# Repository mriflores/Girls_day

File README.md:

# 433MHz RF Communication Project with ID Filtering & Servo Control

This project implements a wireless communication system between two Arduino boards using 433MHz Radio Frequency modules. It features a custom ID filtering system to ensure messages are processed only by the intended receiver, and allows for remote control of a servo motor.

---

## Hardware Configuration

### Components Required
* **Microcontrollers:** 2x Arduino Uno.
* **RF Kit:** 2x 433MHz Transmitter (FS1000A), 1x 433MHz Receiver (XY-MX-5V).
* **Actuator:** 1x Servo Motor (e.g., SG90, MG996R).
* **Antennas:** 4x 17.3 cm copper wires (Required for range beyond 10cm).

### RF Wiring Diagram

| RF Module | Arduino Pin | Description |
| :--- | :--- | :--- |
| **Transmitter DATA** | D12 | Data Output |
| **Transmitter VCC** | 5V | Power (Up to 12V for range) |
| **Transmitter GND** | GND | Ground |
| **Receiver DATA** | D11 | Data Input |
| **Receiver VCC** | 5V | Power (Must be stable 5V) |
| **Receiver GND** | GND | Ground |

### Servo Wiring Diagram

| Servo | Arduino Pin | Description |
| :--- | :--- | :--- |
| **Signal (Orange/Yellow)**| D2 | PWM Control Signal |
| **VCC (Red)** | 5V | Power (External power recommended for larger servos) |
| **GND (Brown/Black)** | GND | Ground |

---

## Technical Implementation & Dependencies

The system relies on specific libraries to manage the communication and motor control without hardware timer conflicts:

* **RadioHead (RH_ASK):** Handles the physical layer bit-streaming, preamble, and CRC error checking for the RF modules. It inherently relies on Arduino's Timer 1.
* **ServoTimer2:** Manages the PWM signals for the servo motor. Using this library instead of the standard Arduino `Servo.h` is necessary to prevent Timer 1 conflicts, ensuring both RF communication and servo movements work seamlessly together.

---

## Features

* **Targeted Messaging:** Uses custom ID prefixes to ensure that only the designated receiver acts on a broadcasted message, ignoring irrelevant data.
* **Remote Actuation:** Wirelessly controls a servo motor, interpreting text strings to execute specific physical movements.
* **Dynamic Pulse Mapping:** Automatically maps standard angle values (0-180 degrees) to microsecond pulse widths for accurate servo positioning.

---

## Command Protocol

The transmitter must format strings with a specific structure for the receiver to validate and act upon them. The structure is: 

`[RECEIVER_ID] [COMMAND]`

### Example Usage:
In this project, the Receiver's ID is set to `100`. Through the Serial Monitor, you can send the following commands:

* **`100 OPEN`**: The receiver parses the ID, confirms a match, and moves the servo to the 90-degree position.
* **`100 CLOSE`**: The receiver parses the ID, confirms a match, and returns the servo to the 0-degree position.

Any message received with an incorrect ID (e.g., `300 OPEN` or just `OPEN`) will be completely ignored by the receiving node.

---

## Important Notes
* **Power Supply:** If the Arduino resets or the RF receiver stops working when the servo moves, it is highly recommended to power the servo with a separate 5V power supply. Remember to connect the ground (GND) of the external power supply to the Arduino's GND.

---

The uploaded image illustrates the specific wiring connections for two separate microcontroller nodes capable of two-way RF communication.

**Node 1** (Top Section)
    This node acts as the primary controller equipped with actuation capabilities.

* Microcontroller: Arduino Uno (U1).

* RF Transmitter (U2 - FS1000A): The Data pin is wired to digital pin D12 (blue wire).

* RF Receiver (U3 - XY-MK-5V): The Data pin is wired to digital pin D11 (green wire).

* Servo Motor (U4): The PWM signal pin is wired to digital pin D2 (orange wire).

Power: All three peripherals (U2, U3, U4) share common 5V (red wires) and Ground (black wires) connections drawn directly from the Arduino Uno.

**Node 2** (Bottom Section)
    This node acts as the secondary transceiver.

* Microcontroller: A compact Arduino board, such as a Nano or Micro (U5).

* RF Transmitter (U6 - FS1000A): The Data pin is wired to digital pin D12 (blue wire).

* RF Receiver (U7 - XY-MK-5V): The Data pin is wired to digital pin D11 (green wire).

Power: Both RF modules draw 5V (red wires) and Ground (black wires) from the compact Arduino board.

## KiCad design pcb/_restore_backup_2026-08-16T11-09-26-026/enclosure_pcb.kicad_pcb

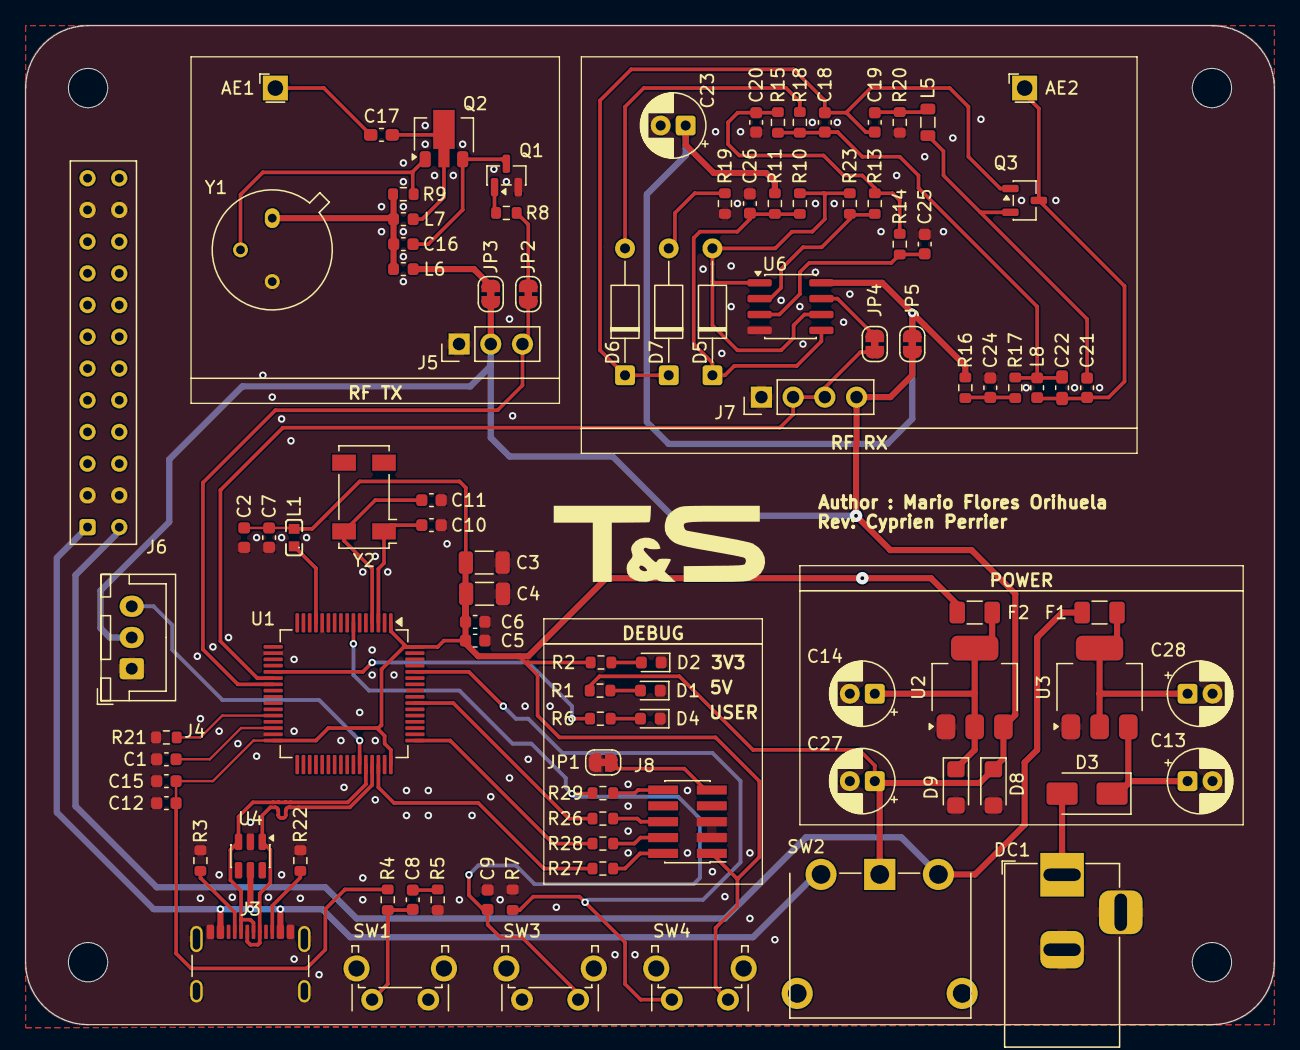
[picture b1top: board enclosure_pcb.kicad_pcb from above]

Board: 2 copper layers, 100.0 x 80.0 mm, 102 parts (0 on the bottom side), 60 nets.

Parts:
AE1, AE2: Antenna; AntennaHole
C1, C26: 4.7uF; C_0603_1608Metric
C2, C9: 100nF; C_0603
C3, C4: 100nF; C_1206_3216Metric
C5, C6, C8: 100nF; C_0603_1608Metric
C7, C12, C15, C25: 1uF; C_0603_1608Metric
C10, C11: 6.8pF; C_0603_1608Metric
C13: 1uF; CP_Radial_D5.0mm_P2.00mm
C14: 100uF; CP_Radial_D5.0mm_P2.00mm
C16: 7pF; C_0603_1608Metric
C17: 7pF; C_0603_1608Metric_Pad1.08x0.95mm_HandSolder
C18: 33pF; C_0603_1608Metric
C19, C20: 1nF; C_0603_1608Metric
C21: 2pF; C_0603_1608Metric
C22: 2pF; C_0603_1608Metric_Pad1.08x0.95mm_HandSolder
C23, C27: 10uF; CP_Radial_D5.0mm_P2.00mm
C24: 47uF; C_0603_1608Metric
C28: 4.7uF; CP_Radial_D5.0mm_P2.00mm
D1, D2: VLMS1300-GS08; LED_0603_1608Metric
D3: D; D_SMA
D4: Blue; LED_0603_1608Metric
D5, D6, D7: 1N4148_C402212; D_DO-35_SOD27_P10.16mm_Horizontal
D8: PLZ5V1B; D_SMF
D9: PLZ3V3B; D_SMF
DC1: DC-005-A200; BarrelJack_Horizontal
F1, F2: Polyfuse; Fuse_1206_3216Metric
H2, H3, H4, H5: MountingHole; MountingHole_2.1mm
J3: USB_C_Receptacle_USB2.0_14P; USB_C_Receptacle_GCT_USB4105-xx-A_16P_TopMnt_Horizontal
J4: Conn_01x03_Pin; JST_XH_B3B-XH-A_1x03_P2.50mm_Vertical
J5: Conn_01x03_Pin; PinHeader_1x03_P2.54mm_Vertical
J6: Conn_02x12_Odd_Even; Samtec_HLE-112-02-xx-DV-TE_2x12_P2.54mm_Horizontal
J7: Conn_01x04_Pin; PinHeader_1x04_P2.54mm_Vertical
J8: Conn_ARM_JTAG_SWD_10; PinHeader_2x05_P1.27mm_Vertical_SMD
JP1, JP2, JP3, JP4, JP5: SolderJumper_2_Bridged; SolderJumper-2_P1.3mm_Bridged_RoundedPad1.0x1.5mm
L1: FCM1608KF-601T05; L0603
L5: 2uH; L_0805_2012Metric
L6: 180nH; L_0603_1608Metric
L7: 36nH; L_0603_1608Metric
L8: 15nH; L_0603_1608Metric
Q1: S8050; SOT-23
Q2: 2SC3357-T1-A; SOT-89-3
Q3: MMBT918; SOT-23-3
R1: 180Ω; R_0603_1608Metric
R2, R5: 100Ω; R_0603_1608Metric
R3, R22: 5k1R; R_0603_1608Metric
R4: 4.7kΩ; R_0603_1608Metric
R6: 47Ω; R_0603_1608Metric
R7: 10kΩ; R_0603
R8, R9: 27kΩ; R_0603_1608Metric
R10: 47kΩ; R_0603_1608Metric
R11: 3MΩ; R_0603_1608Metric
R13, R14: 100kΩ; R_0603_1608Metric
R15: 5.6kΩ; R_0603_1608Metric
R16: 10Ω; R_0603_1608Metric
R17: 12kΩ; R_0603_1608Metric
R18: 20kΩ; R_0603_1608Metric
R19: 18kΩ; R_0603_1608Metric
R20: 680kΩ; R_0603_1608Metric
R21: 10kΩ; R_0603_1608Metric
R23: 6.8MΩ; R_0603_1608Metric
R26, R27, R28, R29: 22Ω; R_0603_1608Metric
SW1, SW3, SW4: SW_Push_WE; SW_Tactile_SPST_Angled_WE
SW2: SW_Lever_RSPRO_5MS1
U1: STM32F446RETx; LQFP-64_10x10mm_P0.5mm
U2: LD1117S33TR_SOT223; SOT-223-3_TabPin2
U3: LD1117S50TR_SOT223; SOT-223-3_TabPin2
U4: USBLC6-4SC6; SOT-23-6
U6: LM358_C5252902; SOIC-8_3.9x4.9mm_P1.27mm
Y1: Crystal_GND3; TO-39-3
Y2: Crystal_4-pin; Crystal_SMD_Abracon_ABS25-4Pin_8.0x3.8mm

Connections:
+3.3VA: L1.1, U1.13 (VDDA)
+3V3: C2.1, C3.1, C4.1, C5.1, C6.1, C7.1, C12.1, C15.1, F2.1, J6.23, J8.1 (VTref), L1.2, R2.1, R4.1, SW4.3, U1.1 (VBAT), U1.19 (VDD), U1.32 (VDD), U1.48 (VDD), U1.64 (VDD)
+5V: C27.1, D8.1 (K), J4.2, J5.2, J6.24, J7.4, JP3.1 (A), JP5.1 (A), R1.1, SW2.2 (B), U2.3 (VI)
+E5V: F1.1, J6.2, SW2.3 (C)
+U5V: J3.A4 (VBUS), J3.A9 (VBUS), J3.B4 (VBUS), J3.B9 (VBUS), J6.1, SW2.1 (A), U4.5 (VBUS)
/SCH_FS1000/5V_FS: JP3.2 (B), L6.1
/SCH_FS1000/5V_XY: C23.1, JP5.2 (B), R11.1, R16.2, U6.8 (VCC)
/SCH_FS1000/DATA IN: J7.2, J7.3, JP4.1 (A), U1.22 (PA6)
/SCH_FS1000/DATA OUT: J5.3, JP2.1 (A), U1.23 (PA7)
/SCH_FS1000/DATA_IN_XY: JP4.2 (B), U6.7 (OUT2)
/SCH_FS1000/DATA_OUT_FS: JP2.2 (B), R8.1
/SCH_MCU/LED: R6.1, U1.21 (PA5)
/SCH_MCU/NRST: C9.2, R29.2, SW3.3, U1.7 (NRST)
/SCH_MCU/OSC32_IN: C10.1, U1.3 (PC14), Y2.1
/SCH_MCU/OSC32_OUT: C11.1, U1.4 (PC15), Y2.4
/SCH_MCU/PUSH_BTN: C8.1, R4.2, SW1.2, U1.2 (PC13)
/SCH_MCU/PWM: J4.3, U1.43 (PA10)
/SCH_MCU/SWCLK: R28.2, U1.49 (PA14)
/SCH_MCU/SWDIO: R27.2, U1.46 (PA13)
/SCH_MCU/SWO: R26.2, U1.55 (PB3)
/SCH_MCU/U_D_N: J3.A7 (D-), J3.B7 (D-), U1.44 (PA11), U4.3 (I/O2)
/SCH_MCU/U_D_P: J3.A6 (D+), J3.B6 (D+), U1.45 (PA12), U4.1 (I/O1)
GND: C1.2, C2.2, C3.2, C4.2, C5.2, C6.2, C7.2, C9.1, C10.2, C11.2, C12.2, C13.2, C14.2, C15.2, C20.2, C23.2, C24.2, C25.2, C26.2, C27.2, C28.2, D1.1 (K), D2.1 (K), D4.1, D8.2 (A), D9.2 (A), DC1.2, DC1.3, J3.A1 (GND), J3.A12 (GND), J3.B1 (GND), J3.B12 (GND), J3.SH (SHIELD), J4.1, J5.1, J6.3, J6.4, J6.21, J6.22, J7.1, J8.3 (GND), J8.5 (GND), JP1.1 (A), Q1.2 (E), R3.1, R5.1, R7.2, R19.2, R20.2, R21.2, R22.2, SW1.1, SW1.3, SW1.4, SW3.1, SW3.2, SW3.4, SW4.1, SW4.4, U1.12 (VSSA), U1.18 (VSS), U1.31 (VSS), U1.47 (VSS), U1.63 (VSS), U2.1 (GND), U3.1 (GND), U4.2 (GND), U6.4 (VEE), Y1.3
unnamed: AE1.1 (A_1), C17.1
unnamed: AE2.1 (A_1), C21.2, C22.1, L8.1, Q3.3 (C)
unnamed: C8.2, R5.2
unnamed: C16.2, L6.2, L7.1, R9.1, Y1.1
unnamed: C18.1, C22.2, L8.2, R15.1, R17.2, R18.1
unnamed: C19.2, L5.1, R20.1
unnamed: C20.1, R13.1, R14.1, R15.2
unnamed: C24.1, R16.1, R17.1
unnamed: D1.2 (A), R1.2
unnamed: D2.2 (A), R2.2
unnamed: D3.2 (A), DC1.1
unnamed: D4.2, R6.2
unnamed: D5.2 (A), R10.1, R23.2, U6.1 (OUT1), U6.6 (IN2-)
unnamed: C26.1, D5.1 (C), R10.2, R11.2, U6.5 (IN2+)
unnamed: D6.2 (A), R18.2
unnamed: C18.2, C19.1, D6.1 (C), D7.1 (C), Q3.1 (B)
unnamed: D7.2 (A), R19.1
unnamed: C14.1, D9.1 (K), F2.2, U2.2 (VO)
unnamed: J3.A5 (CC1), R3.2
unnamed: J3.B5 (CC2), R22.1
unnamed: J8.9 (GNDDetect), JP1.2 (B)
unnamed: J8.4 (SWCLK/TCK), R28.1
unnamed: J8.2 (SWDIO/TMS), R27.1
unnamed: J8.6 (SWO/TDO), R26.1
unnamed: J8.10 (~RESET), R29.1
unnamed: Q1.1 (B), R8.2
unnamed: C16.1, Q1.3 (C), Q2.3 (E)
unnamed: Q2.1 (B), R9.2, Y1.2
unnamed: C17.2, L7.2, Q2.2 (C)
unnamed: C21.1, L5.2, Q3.2 (E)
unnamed: R7.1, SW4.2, U1.60 (BOOT0)
unnamed: R21.1, U1.28 (PB2)
unnamed: C1.1, U1.30 (VCAP_1)
unnamed: C28.1, F1.2, U3.2 (VO)
unnamed: C25.1, R14.2, U6.3 (IN1+)
unnamed: R13.2, R23.1, U6.2 (IN1-)
VIN: C13.1, D3.1 (K), U3.3 (VI)

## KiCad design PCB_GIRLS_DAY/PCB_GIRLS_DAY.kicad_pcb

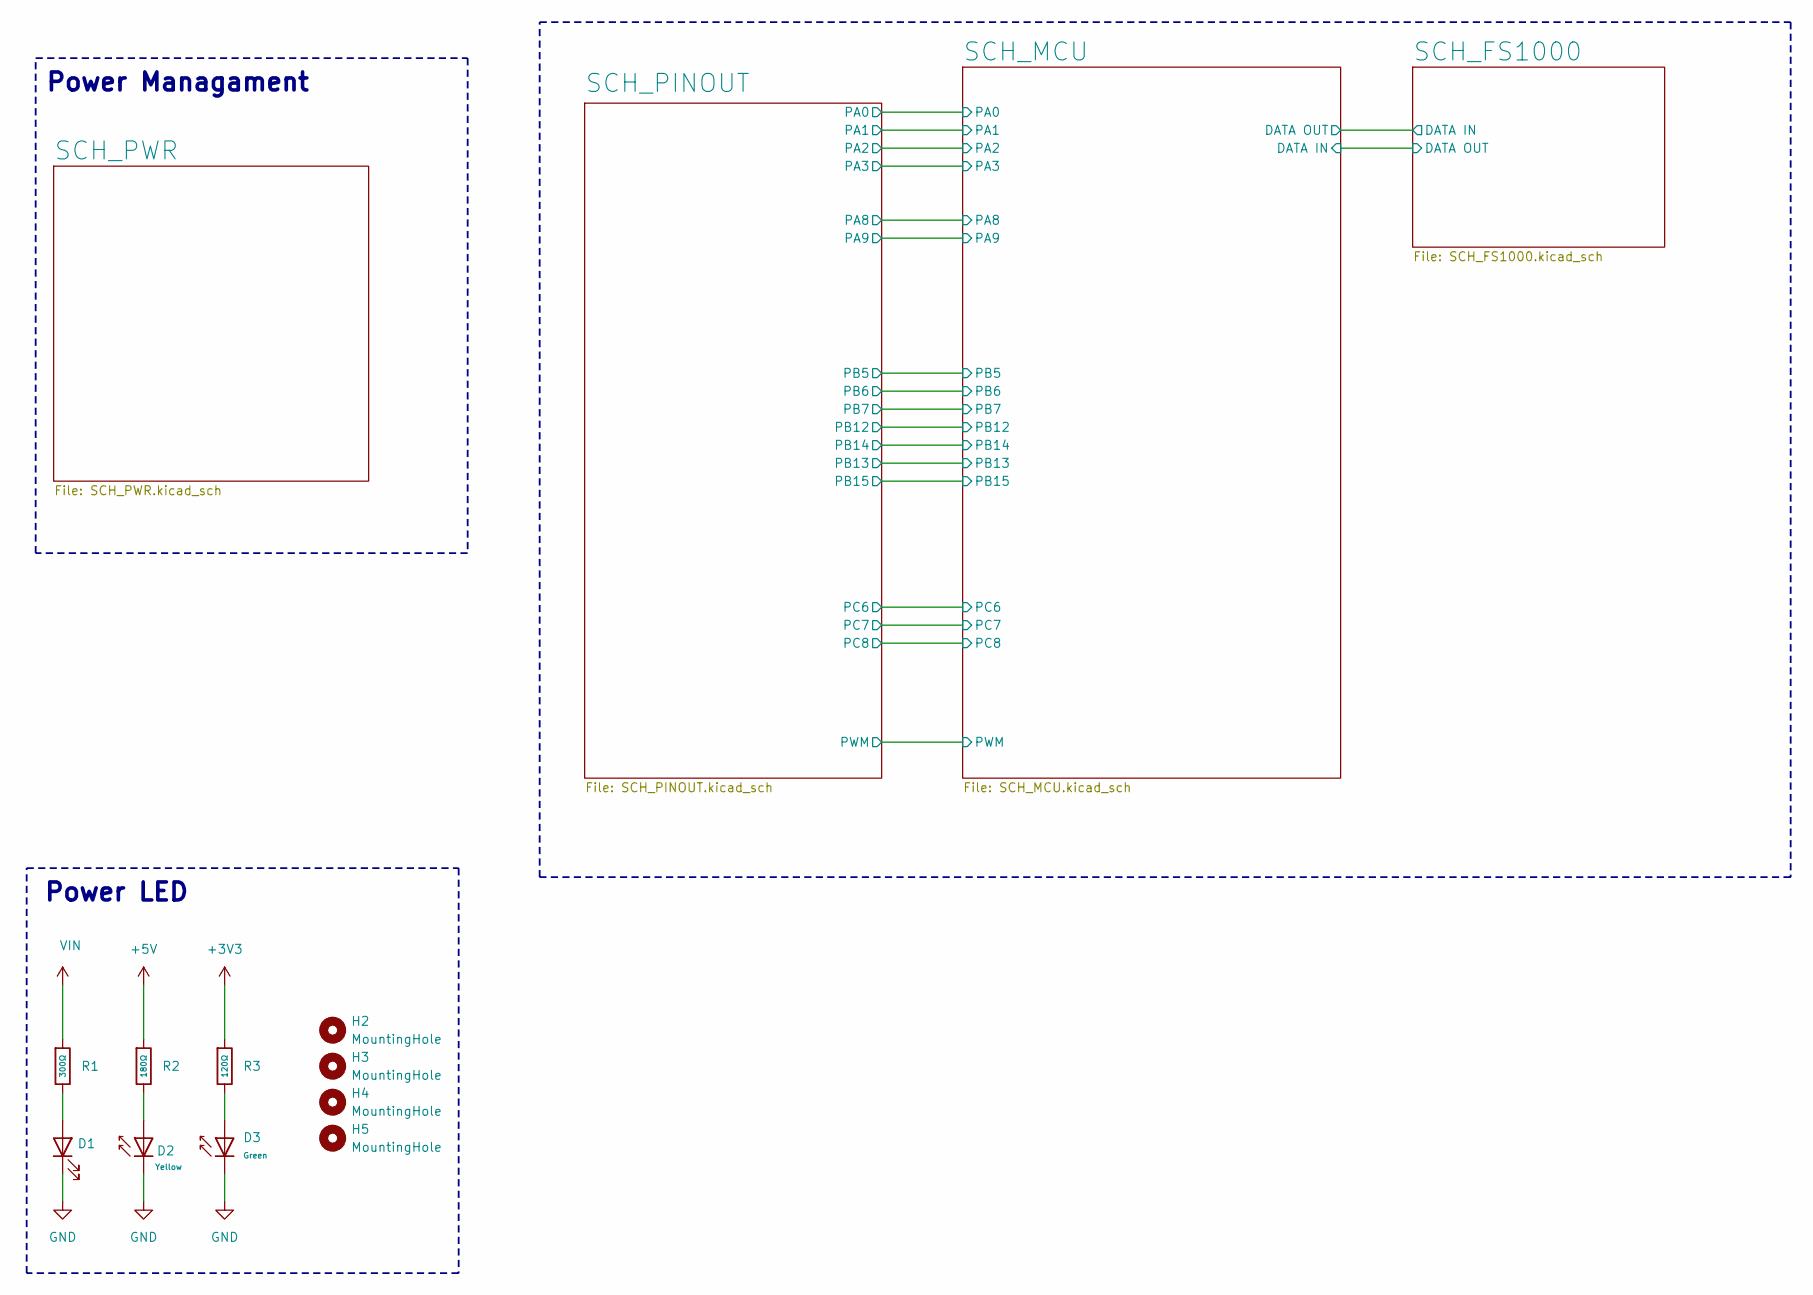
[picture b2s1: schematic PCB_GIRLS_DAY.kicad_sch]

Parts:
D1: IR26-21C_L110_TR8; LED_1206_3216Metric
D2: Yellow; D_0805; Part KT-0805Y; LCSC C2296
D3: Green; D_0805; Part KT-0805G; LCSC C2297
H2, H3, H4, H5: MountingHole; MountingHole_2.1mm
R1: 300Ω; R_1206; Overload Voltage (Max) 200V; Tolerance ±1%; Part 1206W4F3000T5E; LCSC C17887
R2: 180Ω; R_1206; Overload Voltage (Max) 200V; Tolerance ±1%; Part 1206W4F1800T5E; LCSC C17924
R3: 120Ω; R_0805; Overload Voltage (Max) 150V; Tolerance ±1%; Part 0805W8F1200T5E; LCSC C17437

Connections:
+3V3: R3.1; also elsewhere on the board
+5V: R2.1; also elsewhere on the board
GND: D1.1 (K), D2.1, D3.1; also elsewhere on the board
unnamed: D1.2 (A), R1.2
unnamed: D2.2, R2.2
unnamed: D3.2, R3.2
VIN: R1.1; also elsewhere on the board

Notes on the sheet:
Power Managament
Power LED

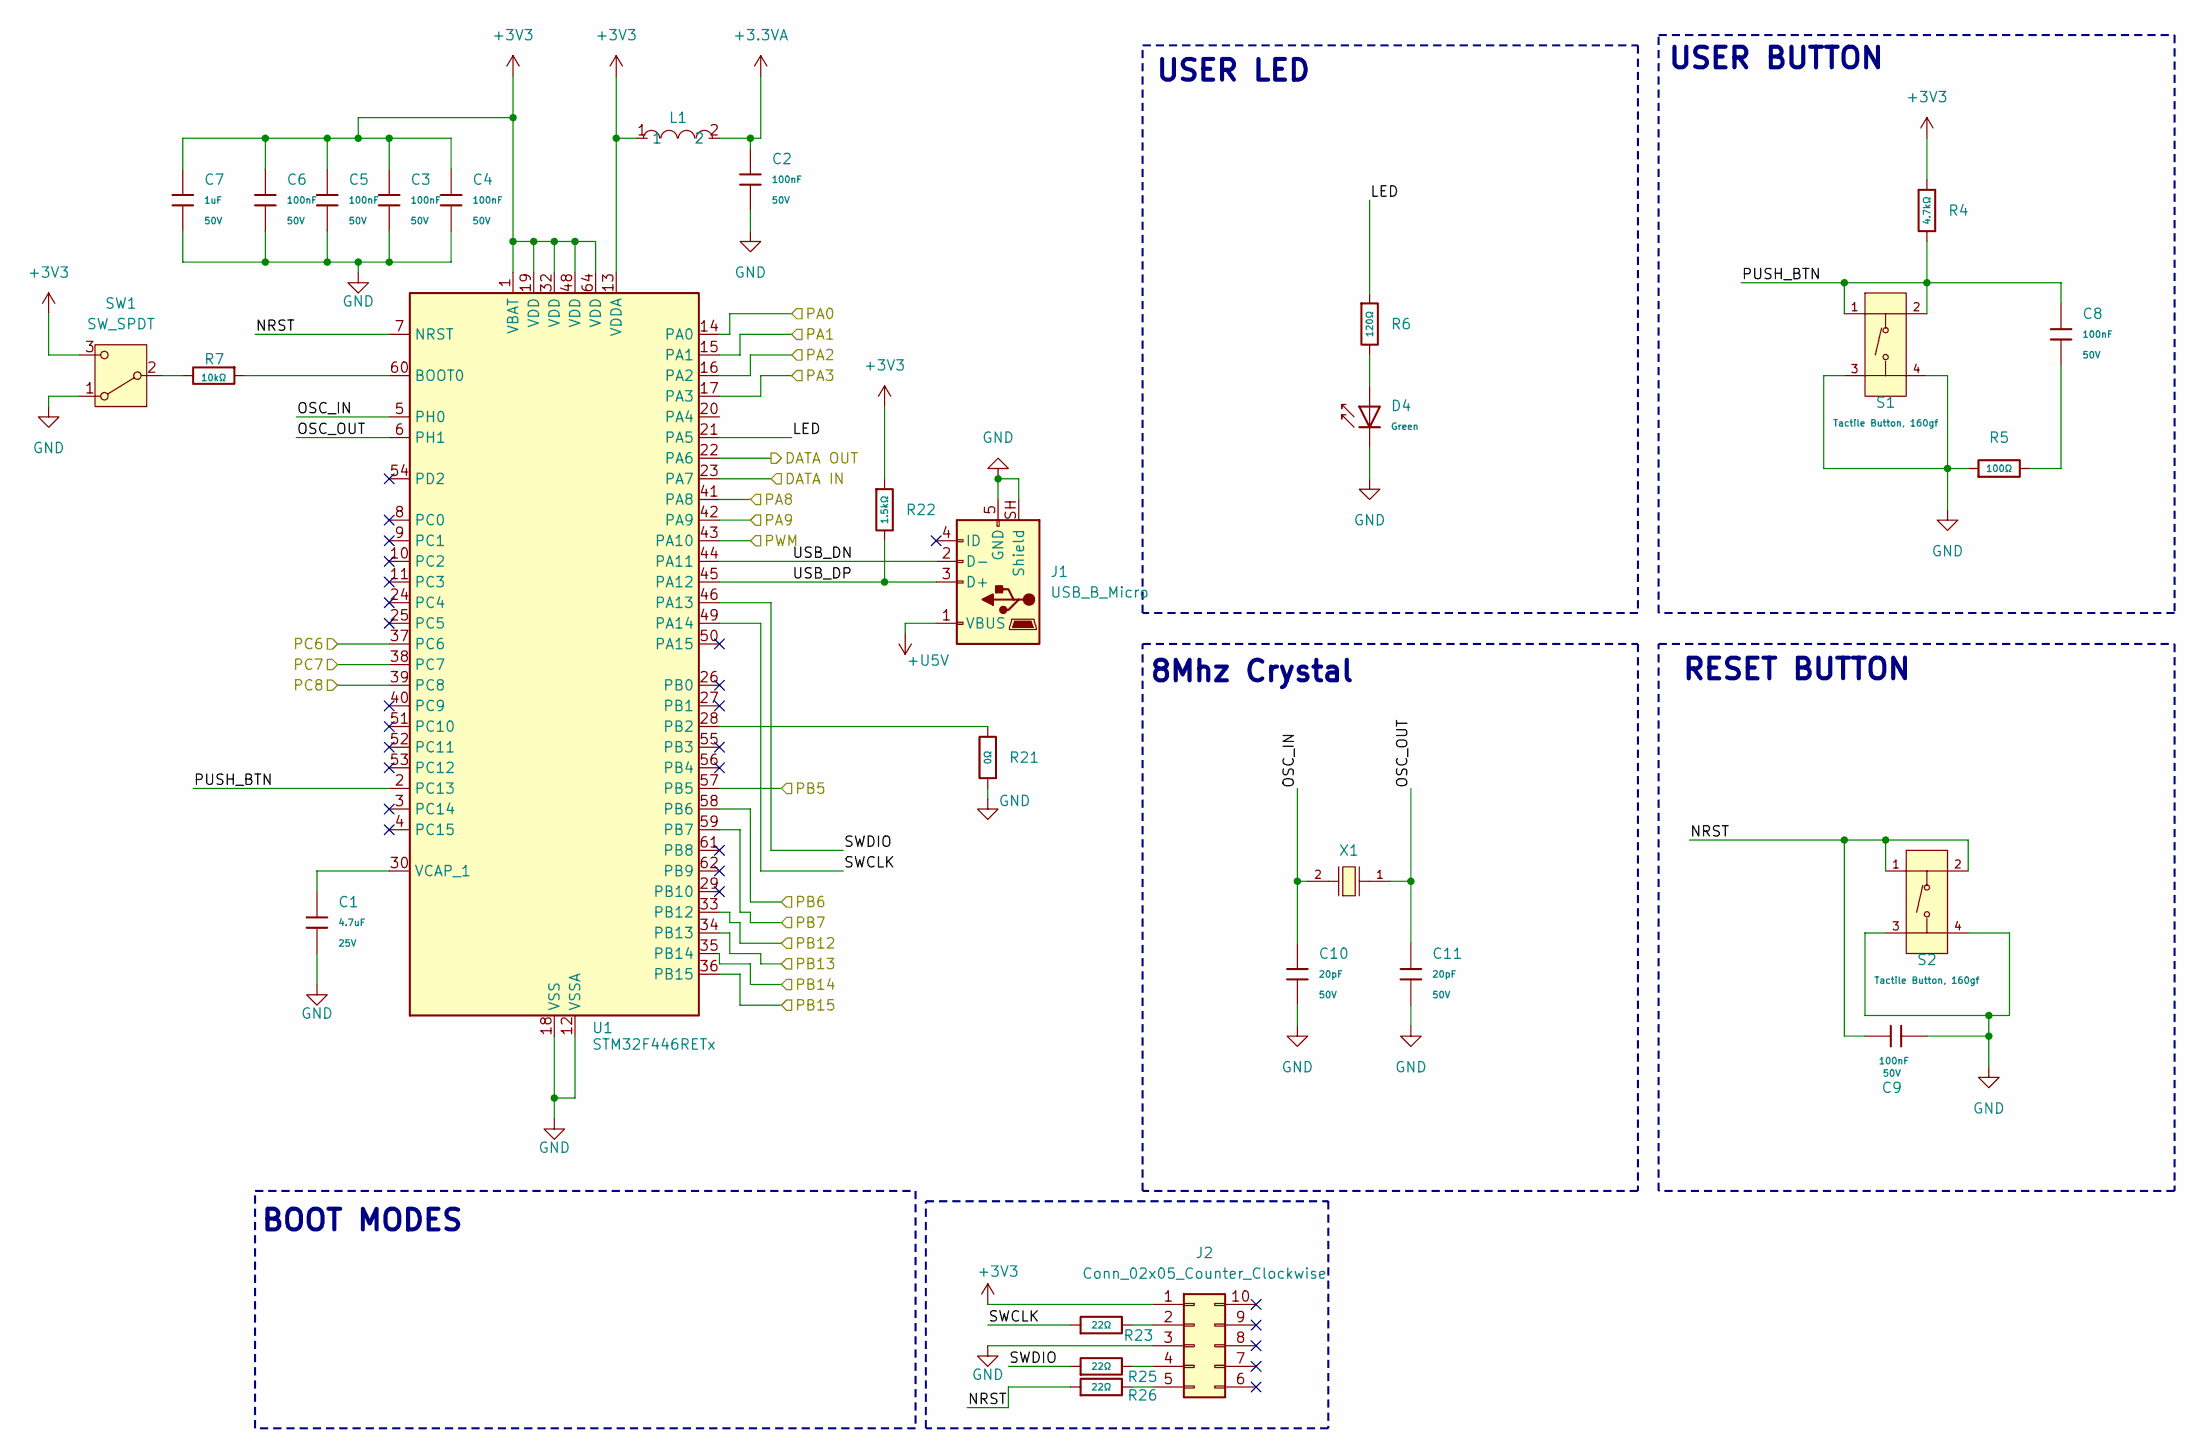
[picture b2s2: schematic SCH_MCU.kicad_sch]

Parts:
C1: 4.7uF; C_0805; Voltage Rated 25V; Tolerance ±10%; Part CL21A475KAQNNNE; LCSC C1779
C2, C3, C4, C5, C6, C8, C9: 100nF; C_0603; Voltage Rated 50V; Tolerance ±10%; Part CC0603KRX7R9BB104; LCSC C14663
C7: 1uF; C_0603; Voltage Rated 50V; Tolerance ±10%; Part CL10A105KB8NNNC; LCSC C15849
C10, C11: 20pF; C_0603; Voltage Rated 50V; Tolerance ±5%; Part CL10C200JB8NNNC; LCSC C1648
D4: Green; D_0805; Part KT-0805G; LCSC C2297
J1: USB_B_Micro; USB_Micro-B_Wuerth_629105150521
J2: Conn_02x05_Counter_Clockwise; Tag-Connect_TC2050-IDC-FP_2x05_P1.27mm_Vertical
L1: FCM1608KF-601T05; L0603; MPN FCM1608KF-601T05; LCSC Part C133937
R4: 4.7kΩ; R_0603; Overload Voltage (Max) 75V; Tolerance ±1%; Part 0603WAF4701T5E; LCSC C23162
R5: 100Ω; R_0603; Overload Voltage (Max) 75V; Tolerance ±1%; Part 0603WAF1000T5E; LCSC C22775
R6: 120Ω; R_0805; Overload Voltage (Max) 150V; Tolerance ±1%; Part 0805W8F1200T5E; LCSC C17437
R7: 10kΩ; R_0603; Overload Voltage (Max) 75V; Tolerance ±1%; Part 0603WAF1002T5E; LCSC C25804
R21: 0Ω; R_0603; Overload Voltage (Max) 75V; Tolerance ±1%; Part 0603WAF0000T5E; LCSC C21189
R22: 1.5kΩ; R_0603; Overload Voltage (Max) 75V; Tolerance ±1%; Part 0603WAF1501T5E; LCSC C22843
R23, R25, R26: 22Ω; R_0603; Overload Voltage (Max) 75V; Tolerance ±1%; Part 0603WAF220JT5E; LCSC C23345
S1, S2: Tactile Button, 160gf; SW-SMD_4P-L5.1-W5.1-P3.70-LS6.5-TL-2; Voltage Rating (Dc) 12V; Part TS-1187A-B-A-B; LCSC C318884
SW1: SW_SPDT; SW_SPDT_PCM12
U1: STM32F446RETx; LQFP-64_10x10mm_P0.5mm
X1: X50328MSB2GI; CRYSTAL-SMD_L5.0-W3.2; Frequency Tolerance ±10ppm; Part X50328MSB2GI; LCSC C115962

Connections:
+3.3VA: C2.1, L1.2
+3V3: C3.1, C4.1, C5.1, C6.1, C7.1, J2.1, L1.1, R4.1, R22.1, SW1.3 (C), U1.1 (VBAT), U1.13 (VDDA), U1.19 (VDD), U1.32 (VDD), U1.48 (VDD), U1.64 (VDD); also elsewhere on the board
+U5V: J1.1 (VBUS); also elsewhere on the board
/SCH_FS1000/DATA IN: U1.22 (PA6); also elsewhere on the board
/SCH_FS1000/DATA OUT: U1.23 (PA7); also elsewhere on the board
/SCH_MCU/LED: R6.1, U1.21 (PA5)
/SCH_MCU/NRST: C9.2, R26.1, S2.1 (A), S2.2 (B), U1.7 (NRST)
/SCH_MCU/OSC_IN: C10.1, U1.5 (PH0), X1.2
/SCH_MCU/OSC_OUT: C11.1, U1.6 (PH1), X1.1
/SCH_MCU/PA0: U1.14 (PA0); also elsewhere on the board
/SCH_MCU/PA1: U1.15 (PA1); also elsewhere on the board
/SCH_MCU/PA2: U1.16 (PA2); also elsewhere on the board
/SCH_MCU/PA3: U1.17 (PA3); also elsewhere on the board
/SCH_MCU/PA8: U1.41 (PA8); also elsewhere on the board
/SCH_MCU/PA9: U1.42 (PA9); also elsewhere on the board
/SCH_MCU/PB5: U1.57 (PB5); also elsewhere on the board
/SCH_MCU/PB6: U1.58 (PB6); also elsewhere on the board
/SCH_MCU/PB7: U1.59 (PB7); also elsewhere on the board
/SCH_MCU/PB12: U1.33 (PB12); also elsewhere on the board
/SCH_MCU/PB13: U1.34 (PB13); also elsewhere on the board
/SCH_MCU/PB14: U1.35 (PB14); also elsewhere on the board
/SCH_MCU/PB15: U1.36 (PB15); also elsewhere on the board
/SCH_MCU/PC6: U1.37 (PC6); also elsewhere on the board
/SCH_MCU/PC7: U1.38 (PC7); also elsewhere on the board
/SCH_MCU/PC8: U1.39 (PC8); also elsewhere on the board
/SCH_MCU/PUSH_BTN: C8.1, R4.2, S1.1 (A), S1.2 (B), U1.2 (PC13)
/SCH_MCU/PWM: U1.43 (PA10); also elsewhere on the board
/SCH_MCU/SWCLK: R23.1, U1.49 (PA14)
/SCH_MCU/SWDIO: R25.1, U1.46 (PA13)
/SCH_MCU/USB_DN: J1.2 (D-), U1.44 (PA11)
/SCH_MCU/USB_DP: J1.3 (D+), R22.2, U1.45 (PA12)
GND: C1.2, C2.2, C3.2, C4.2, C5.2, C6.2, C7.2, C9.1, C10.2, C11.2, D4.1, J1.5 (GND), J1.SH (Shield), J2.3, R5.1, R21.1, S1.3 (C), S1.4 (D), S2.3 (C), S2.4 (D), SW1.1 (A), U1.12 (VSSA), U1.18 (VSS), U1.31 (VSS), U1.47 (VSS), U1.63 (VSS); also elsewhere on the board
unnamed: C8.2, R5.2
unnamed: D4.2, R6.2
unnamed: J2.2, R23.2
unnamed: J2.4, R25.2
unnamed: J2.5, R26.2
unnamed: R7.2, SW1.2 (B)
unnamed: R7.1, U1.60 (BOOT0)
unnamed: R21.2, U1.28 (PB2)
unnamed: C1.1, U1.30 (VCAP_1)

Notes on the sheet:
USER LED
8Mhz Crystal
BOOT MODES
USER BUTTON
RESET BUTTON

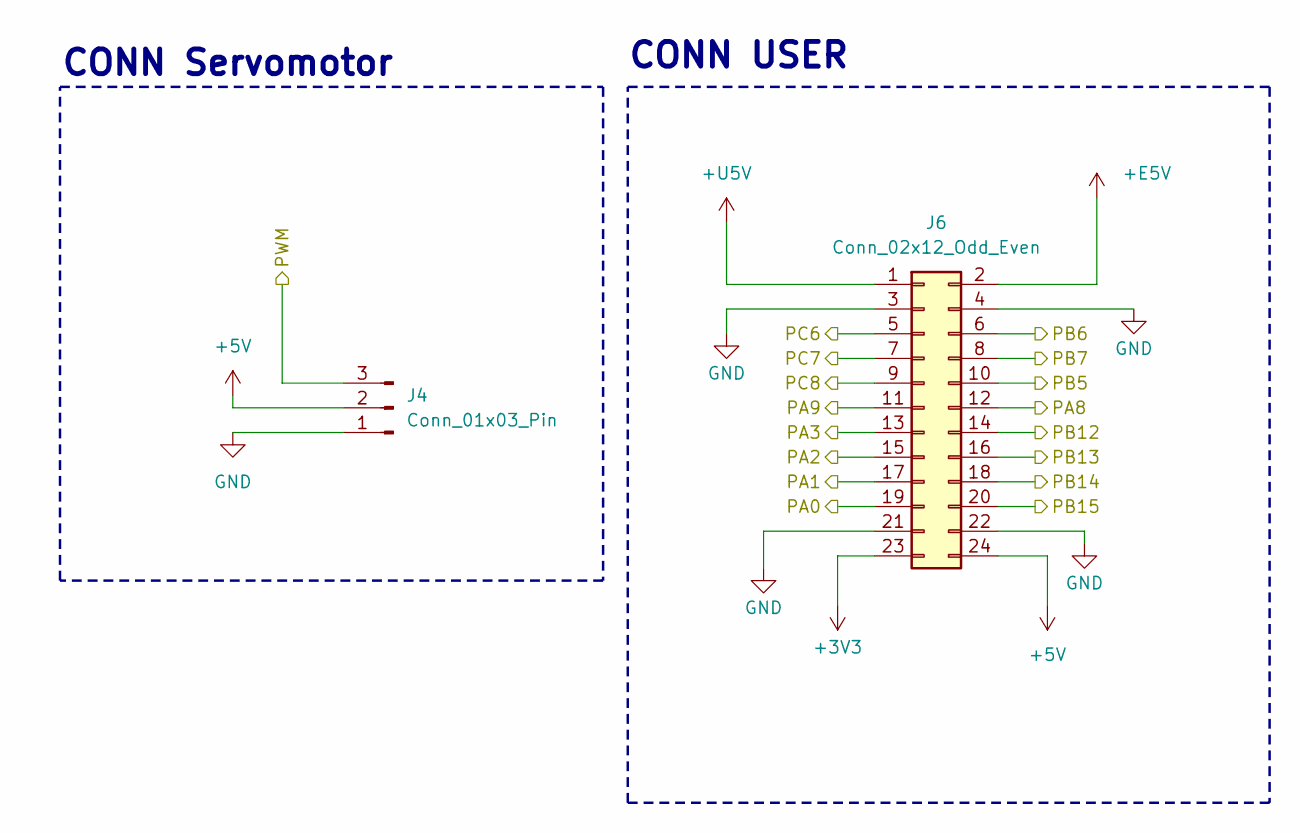
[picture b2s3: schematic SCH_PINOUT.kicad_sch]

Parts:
J4: Conn_01x03_Pin; PinHeader_1x03_P2.54mm_Vertical
J6: Conn_02x12_Odd_Even; Samtec_HLE-112-02-xx-DV-TE_2x12_P2.54mm_Horizontal

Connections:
+3V3: J6.23; also elsewhere on the board
+5V: J4.2, J6.24; also elsewhere on the board
+E5V: J6.2; also elsewhere on the board
+U5V: J6.1; also elsewhere on the board
/SCH_MCU/PA0: J6.19; also elsewhere on the board
/SCH_MCU/PA1: J6.17; also elsewhere on the board
/SCH_MCU/PA2: J6.15; also elsewhere on the board
/SCH_MCU/PA3: J6.13; also elsewhere on the board
/SCH_MCU/PA8: J6.12; also elsewhere on the board
/SCH_MCU/PA9: J6.11; also elsewhere on the board
/SCH_MCU/PB5: J6.10; also elsewhere on the board
/SCH_MCU/PB6: J6.6; also elsewhere on the board
/SCH_MCU/PB7: J6.8; also elsewhere on the board
/SCH_MCU/PB12: J6.14; also elsewhere on the board
/SCH_MCU/PB13: J6.16; also elsewhere on the board
/SCH_MCU/PB14: J6.18; also elsewhere on the board
/SCH_MCU/PB15: J6.20; also elsewhere on the board
/SCH_MCU/PC6: J6.5; also elsewhere on the board
/SCH_MCU/PC7: J6.7; also elsewhere on the board
/SCH_MCU/PC8: J6.9; also elsewhere on the board
/SCH_MCU/PWM: J4.3; also elsewhere on the board
GND: J4.1, J6.3, J6.4, J6.21, J6.22; also elsewhere on the board

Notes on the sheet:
CONN Servomotor
CONN USER

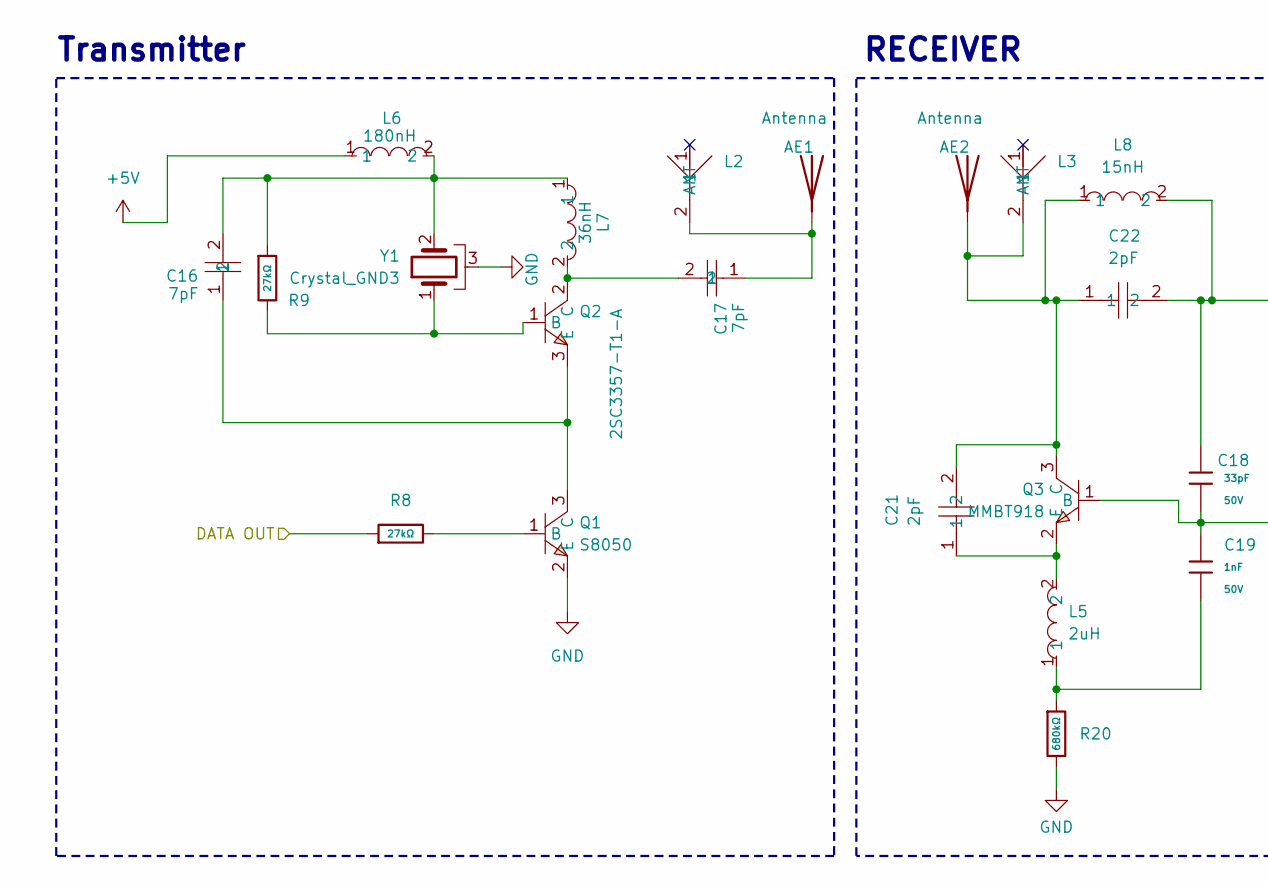
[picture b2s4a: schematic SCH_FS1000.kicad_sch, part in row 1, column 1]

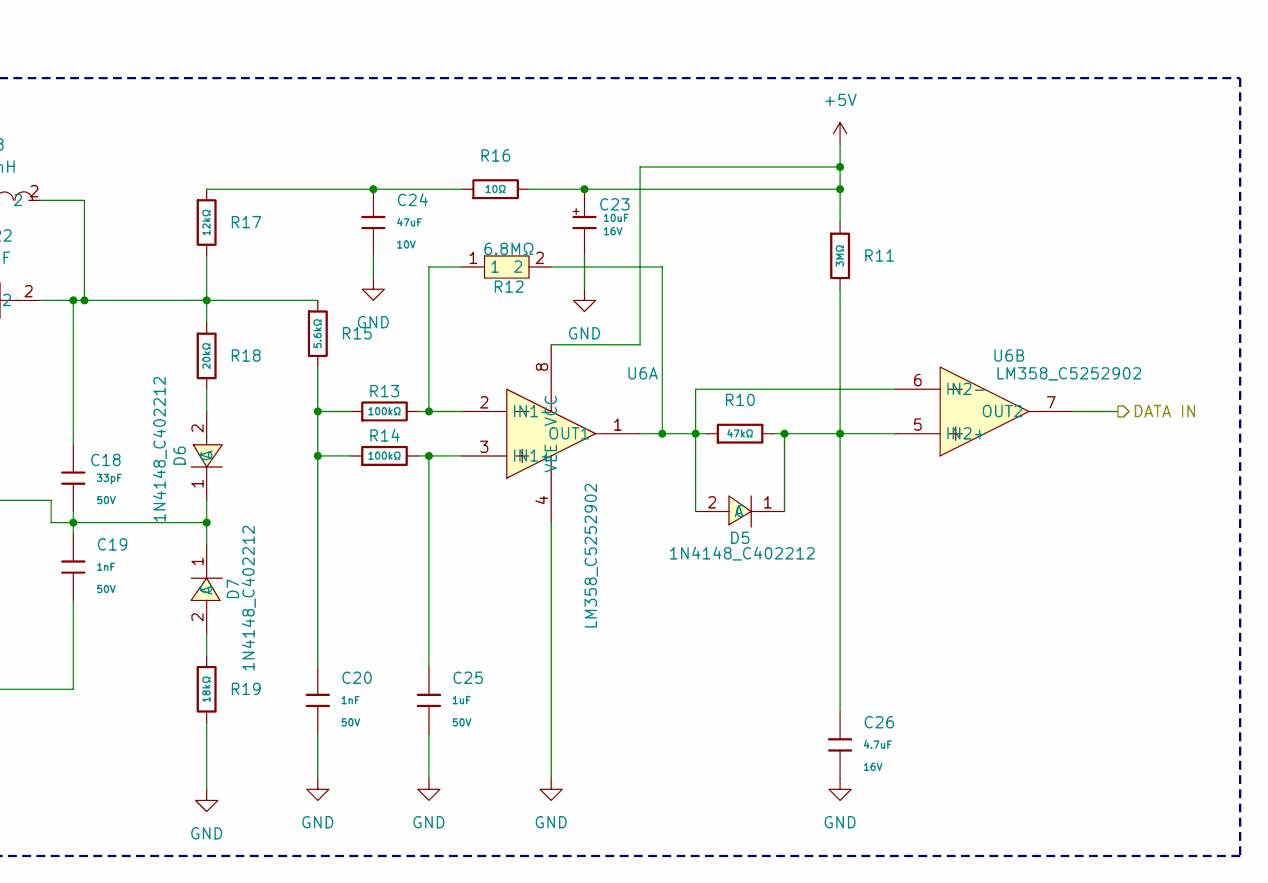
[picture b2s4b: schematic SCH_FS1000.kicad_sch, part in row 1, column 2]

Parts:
AE1, AE2: Antenna; Samtec_HPM-01-01-x-S_Straight_1x01_Pitch5.08mm
C16: 7pF; C_0603_1608Metric; MPN 0603CG7R0C500NT; LCSC Part C1682
C17: 7pF; C_0603_1608Metric_Pad1.08x0.95mm_HandSolder; MPN 0603CG7R0C500NT; LCSC Part C1682
C18: 33pF; C_0603; Voltage Rated 50V; Tolerance ±5%; Part CL10C330JB8NNNC; LCSC C1663
C19, C20: 1nF; C_0603; Voltage Rated 50V; Tolerance ±10%; Part CL10B102KB8NNNC; LCSC C1588
C21, C22: 2pF; C_0603_1608Metric_Pad1.08x0.95mm_HandSolder; MPN CC0603BRNPO9BN2R0; LCSC Part C513620
C23: 10uF; C_CASE-A-3216-18(mm); Tolerance ±10%; Rated Voltage 16V; Part TAJA106K016RNJ; LCSC C7171
C24: 47uF; C_1206; Voltage Rated 10V; Tolerance ±20%; Part CL31A476MPHNNNE; LCSC C96123
C25: 1uF; C_0603; Voltage Rated 50V; Tolerance ±10%; Part CL10A105KB8NNNC; LCSC C15849
C26: 4.7uF; C_0603; Voltage Rated 16V; Tolerance ±10%; Part CL10A475KO8NNNC; LCSC C19666
D5, D6, D7: 1N4148_C402212; DO-35_BD2.0-L4.2-P8.20-D0.5-RD; MPN 1N4148; LCSC Part C402212
L2, L3: BW433MNX1304; ANT-SMD_L130-W42_BW433MNX; MPN BW433MNX1304; LCSC Part C49330093
L5: 2uH; IND-SMD_L10.2-W10.2-LS10.8; MPN IHLP4040DZER2R0M11; LCSC Part C554005
L6: 180nH; IND-SMD_L1.8-W1.2; MPN AISC-0603-R18J-T; LCSC Part C186904
L7: 36nH; IND-SMD_L1.0-W0.5-2; MPN LQW15AN36NG00D; LCSC Part C167476
L8: 15nH; IND-SMD_L1.0-W0.5-2; MPN LQW15AN15NG00D; LCSC Part C98055
Q1: S8050; SOT-23-3_L2.9-W1.3-P1.90-LS2.4-BR; MPN S8050; LCSC Part C916390
Q2: 2SC3357-T1-A; SOT-89-3_L4.5-W2.5-P1.50-LS4.2-BR; MPN 2SC3357-T1-A; LCSC Part C49241781
Q3: MMBT918; SOT-23-3_L2.9-W1.3-P1.90-LS2.4-BR; MPN MMBT918; LCSC Part C184118
R8: 27kΩ; R_0402; Overload Voltage (Max) 50V; Tolerance ±1%; Part 0402WGF2702TCE; LCSC C25771
R9: 27kΩ; R_0603; Overload Voltage (Max) 75V; Tolerance ±1%; Part 0603WAF2702T5E; LCSC C22967
R10: 47kΩ; R_0603; Overload Voltage (Max) 75V; Tolerance ±1%; Part 0603WAF4702T5E; LCSC C25819
R11: 3MΩ; R_0603; Overload Voltage (Max) 75V; Tolerance ±1%; Part 0603WAF3004T5E; LCSC C23156
R12: 6.8MΩ; R1206; MPN FRC1206F6804TS; LCSC Part C3000532
R13, R14: 100kΩ; R_0603; Overload Voltage (Max) 75V; Tolerance ±1%; Part 0603WAF1003T5E; LCSC C25803
R15: 5.6kΩ; R_0603; Overload Voltage (Max) 75V; Tolerance ±1%; Part 0603WAF5601T5E; LCSC C23189
R16: 10Ω; R_0603; Overload Voltage (Max) 75V; Tolerance ±1%; Part 0603WAF100JT5E; LCSC C22859
R17: 12kΩ; R_0603; Overload Voltage (Max) 75V; Tolerance ±1%; Part 0603WAF1202T5E; LCSC C22790
R18: 20kΩ; R_0603; Overload Voltage (Max) 75V; Tolerance ±1%; Part 0603WAF2002T5E; LCSC C4184
R19: 18kΩ; R_0603; Overload Voltage (Max) 75V; Tolerance ±1%; Part 0603WAF1802T5E; LCSC C25810
R20: 680kΩ; R_0603; Overload Voltage (Max) 75V; Tolerance ±1%; Part 0603WAF6803T5E; LCSC C25822
U6: LM358_C5252902; SOP-8_L4.9-W3.9-P1.27-LS6.0-BL; MPN LM358; LCSC Part C5252902
Y1: Crystal_GND3; TO-39-3

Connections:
+5V: C23.1, L6.1, R11.1, R16.2, U6.8 (VCC); also elsewhere on the board
/SCH_FS1000/DATA IN: U6.7 (OUT2); also elsewhere on the board
/SCH_FS1000/DATA OUT: R8.1; also elsewhere on the board
GND: C20.2, C23.2, C24.2, C25.2, C26.2, Q1.2 (E), R19.2, R20.2, U6.4 (VEE), Y1.3; also elsewhere on the board
unnamed: AE1.1 (A_1), C17.1, L2.2 (ANT_2)
unnamed: AE2.1 (A_1), C21.2, C22.1, L3.2 (ANT_2), L8.1, Q3.3 (C)
unnamed: C16.2, L6.2, L7.1, R9.1, Y1.2
unnamed: C18.1, C22.2, L8.2, R15.1, R17.2, R18.1
unnamed: C19.2, L5.1, R20.1
unnamed: C20.1, R13.1, R14.1, R15.2
unnamed: C24.1, R16.1, R17.1
unnamed: D5.2 (A), R10.1, R12.2, U6.1 (OUT1), U6.6 (IN2-)
unnamed: C26.1, D5.1 (C), R10.2, R11.2, U6.5 (IN2+)
unnamed: D6.2 (A), R18.2
unnamed: C18.2, C19.1, D6.1 (C), D7.1 (C), Q3.1 (B)
unnamed: D7.2 (A), R19.1
unnamed: Q1.1 (B), R8.2
unnamed: C16.1, Q1.3 (C), Q2.3 (E)
unnamed: Q2.1 (B), R9.2, Y1.1
unnamed: C17.2, L7.2, Q2.2 (C)
unnamed: C21.1, L5.2, Q3.2 (E)
unnamed: C25.1, R14.2, U6.3 (IN1+)
unnamed: R12.1, R13.2, U6.2 (IN1-)

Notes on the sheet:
Transmitter
RECEIVER

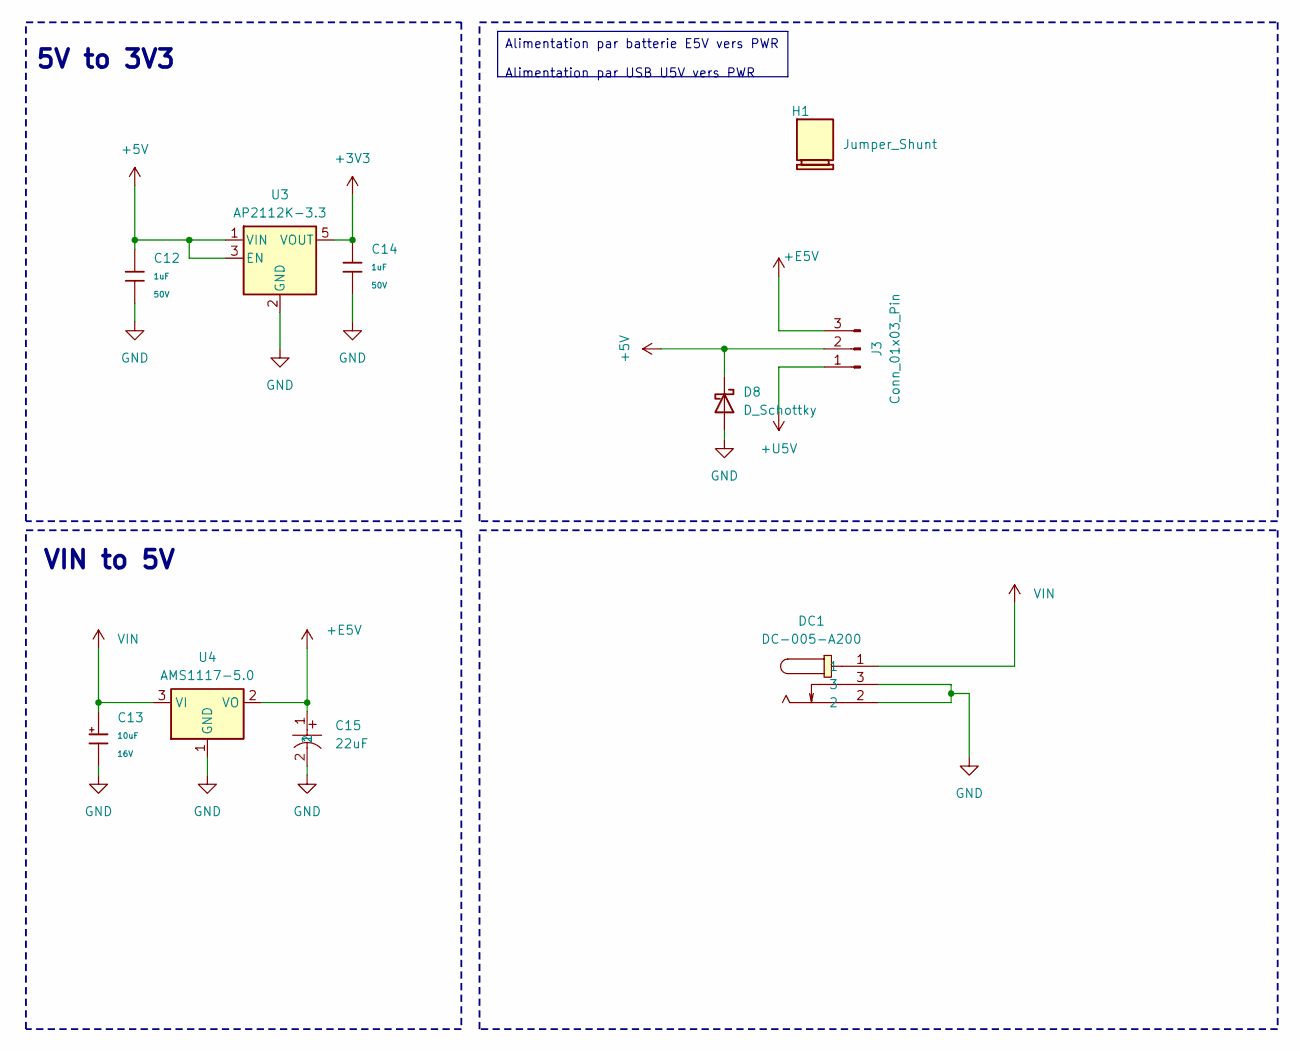
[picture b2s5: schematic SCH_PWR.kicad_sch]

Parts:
C12, C14: 1uF; C_0603; Voltage Rated 50V; Tolerance ±10%; Part CL10A105KB8NNNC; LCSC C15849
C13: 10uF; C_CASE-A-3216-18(mm); Tolerance ±10%; Rated Voltage 16V; Part TAJA106K016RNJ; LCSC C7171
C15: 22uF; CP_Radial_D4.0mm_P2.00mm; MPN RVT1H220M0605; LCSC Part C72505
D8: D_Schottky; D_SOD-323
DC1: DC-005-A200; DC-IN-TH_DC-005-A200; MPN DC-005-A200; LCSC Part C720557
H1: Jumper_Shunt
J3: Conn_01x03_Pin; PinHeader_1x03_P2.54mm_Vertical
U3: AP2112K-3.3; SOT-23-5
U4: AMS1117-5.0; SOT-223-3_TabPin2

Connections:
+3V3: C14.1, U3.5 (VOUT); also elsewhere on the board
+5V: C12.1, D8.1 (K), J3.2, U3.1 (VIN), U3.3 (EN); also elsewhere on the board
+E5V: C15.1, J3.3, U4.2 (VO); also elsewhere on the board
+U5V: J3.1; also elsewhere on the board
GND: C12.2, C13.2, C14.2, C15.2, D8.2 (A), DC1.2, DC1.3, U3.2 (GND), U4.1 (GND); also elsewhere on the board
VIN: C13.1, DC1.1, U4.3 (VI); also elsewhere on the board

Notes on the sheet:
5V to 3V3
VIN to 5V
Alimentation par batterie E5V vers PWR Alimentation par USB U5V vers PWR
